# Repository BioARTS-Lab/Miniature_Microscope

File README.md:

# Miniture_Microscope
3D-printed fluorescence miniature microscope

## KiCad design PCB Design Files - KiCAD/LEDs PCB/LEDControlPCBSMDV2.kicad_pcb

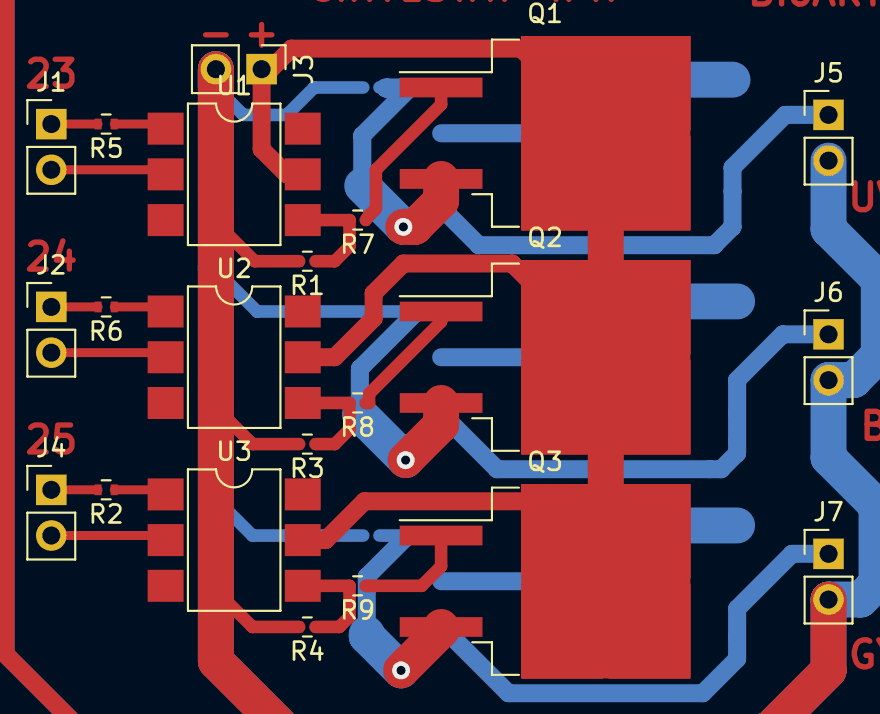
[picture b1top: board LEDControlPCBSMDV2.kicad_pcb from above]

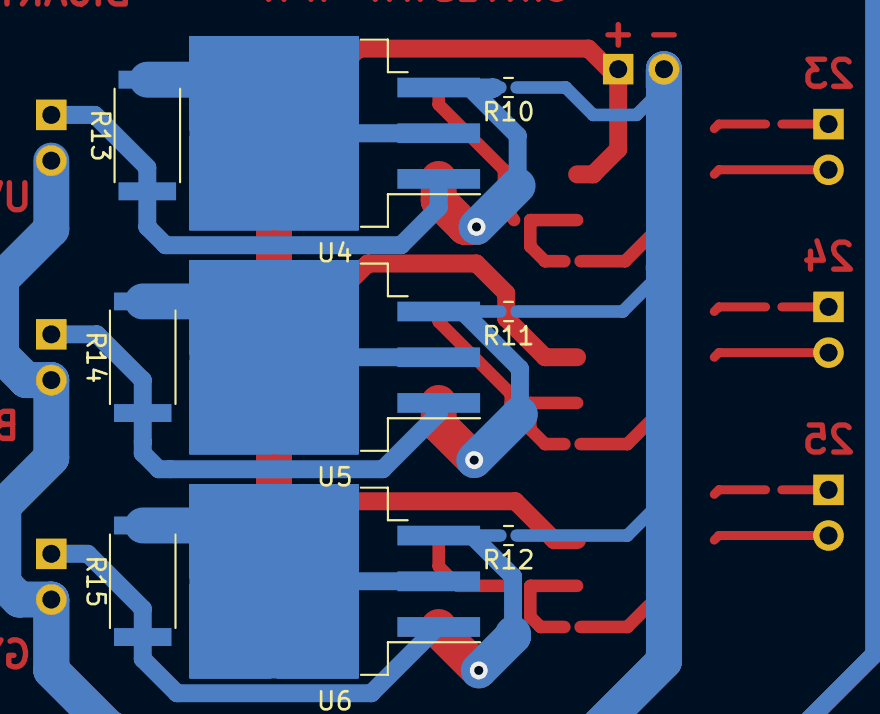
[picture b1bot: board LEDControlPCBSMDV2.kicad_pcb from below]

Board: 2 copper layers, 31 parts (9 on the bottom side), 26 nets.

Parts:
J1, J2, J3, J4, J5, J6, J7: CONN_01X02; Pin_Header_Straight_1x02_Pitch2.54mm
Q1, Q2, Q3: TIP122; TO-263-2
R1, R2, R3, R4, R5, R6, R7, R8, R9, R10, R11, R12: R; R_0402
R13, R14, R15: R; R_2512
U1, U2, U3: 4N25; DIP-6_W7.62mm_SMD
U4, U5, U6: LM317T; TO-263-3_TabPin2

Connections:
GND: J3.2, J5.2, J6.2, J7.2, R1.2, R3.2, R4.2, R10.1, R11.1, R12.1
unnamed: J1.1, R5.2
unnamed: J1.2, U1.2
unnamed: J2.1, R6.2
unnamed: J2.2, U2.2
unnamed: J3.1, Q1.2, Q2.2, Q3.2, U1.5, U2.5, U3.5
unnamed: J4.1, R2.2
unnamed: J4.2, U3.2
unnamed: J5.1, R13.1, U4.1
unnamed: J6.1, R14.1, U5.1
unnamed: J7.1, R15.1, U6.1
unnamed: Q1.1, R7.1
unnamed: Q1.3, R10.2, U4.3
unnamed: Q2.1, R8.1
unnamed: Q2.3, R11.2, U5.3
unnamed: Q3.1, R9.1
unnamed: Q3.3, R12.2, U6.3
unnamed: R1.1, R7.2, U1.4
unnamed: R2.1, U3.1
unnamed: R3.1, R8.2, U2.4
unnamed: R4.1, R9.2, U3.4
unnamed: R5.1, U1.1
unnamed: R6.1, U2.1
unnamed: R13.2, U4.2
unnamed: R14.2, U5.2
unnamed: R15.2, U6.2

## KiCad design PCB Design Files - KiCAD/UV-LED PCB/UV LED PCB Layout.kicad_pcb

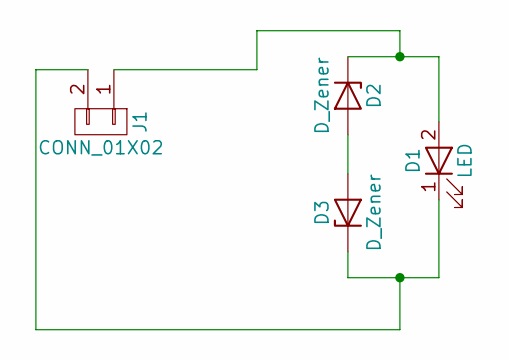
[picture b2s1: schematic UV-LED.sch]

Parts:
D1: LED; VLMU3500
D2, D3: D_Zener; D_A-405_P2.54mm_Vertical_KathodeUp
J1: CONN_01X02; Pin_Header_Angled_1x02_Pitch2.54mm

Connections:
unnamed: D1.1 (K), D3.1 (K), J1.2
unnamed: D1.2 (A), D2.1 (K), J1.1
unnamed: D2.2 (A), D3.2 (A)

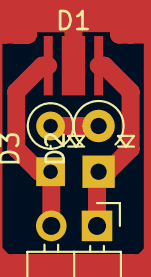
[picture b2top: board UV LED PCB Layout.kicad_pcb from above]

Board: 2 copper layers, 4 parts (0 on the bottom side), 3 nets.
